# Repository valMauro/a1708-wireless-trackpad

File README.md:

# A1708 Wireless Trackpad

**Turn the Force Touch trackpad of a MacBook Pro (A1708, 13" 2016–2017) into a standalone
USB / Bluetooth trackpad, with Mac-style 1:1 gestures.**

*[Leggi in italiano](README.it.md)*

A Raspberry Pi Pico W talks to the trackpad over its native SPI protocol and presents it to the
computer as a **Windows Precision Touchpad** (PTP), over USB, classic Bluetooth or Bluetooth Low
Energy. Windows supports it natively. On macOS, which ignores third-party PTP devices, a small menu-bar app
([macos-trackpad-companion](https://github.com/mathias-sm/macos-trackpad-companion), patched for
this project) turns the raw touches into real macOS gestures: desktop swipes, Mission Control,
pinch, rotate and smooth scrolling that follow the fingers 1:1.

## Features

- **Original Apple hardware**: same glass, same Force Touch click with haptic feedback (generated
  by the trackpad itself).
- **Three connections**: USB-C cable, classic Bluetooth, or **Bluetooth Low Energy** with the
  standard Battery Service, so the battery level shows up in the macOS battery widget and in Windows
  settings.
- **Three paired computers** with one-press switching (like Logitech Easy-Switch), each with its
  own white LED.
- **18650 Li-ion battery** with USB-C charging, a power button, battery indication on the LEDs,
  power saving and an automatic rest mode.
- **Mac-like feel on macOS**: the companion patch uses the *exact* pointer and scroll
  acceleration curves of a MacBook's built-in trackpad, read from macOS itself.
- **Robust firmware**: message validation as in the Linux `applespi` driver, filtering of the
  touch glitches the trackpad produces while vibrating, de-bounced clicks.
- **Firmware updates through the USB-C port** with the case closed: hold buttons 1 and 3 while
  plugging in the cable.
- **All-in-one PCB** (KiCad, ready for JLCPCB assembly) and a **3D-printable wedge case**.

## How it works

```
 A1708 trackpad ──SPI (4 MHz) + 3.3 V / 5 V / 12 V──▶  all-in-one board
                                                         ├─ Raspberry Pi Pico W (firmware)
                                                         ├─ TP4056 charger + 18650 cell
                                                         ├─ MT3608 boost 5 V
                                                         └─ Pololu U3V16F12 boost 12 V (haptics)
        │
        ├─ USB HID ─────────────┐
        ├─ Bluetooth Classic ───┼──▶ Windows: native Precision Touchpad
        └─ Bluetooth LE (HOGP) ─┘    macOS:  Trackpad Companion app ──▶ native gestures
```

## Repository layout

| Folder | Contents |
|---|---|
| [`firmware/`](firmware) | Pico W firmware (C, pico-sdk, TinyUSB, BTstack) and prebuilt `.uf2` files |
| [`hardware/pcb/`](hardware/pcb) | KiCad board, Gerbers, BOM and placement files for JLCPCB |
| [`hardware/case/`](hardware/case) | STL files of the case and their Python source |
| [`macos-companion/`](macos-companion) | Patch for macos-trackpad-companion and a build script |
| [`docs/`](docs) | Build guide, firmware manual, macOS setup, SPI protocol notes |

## Getting started

1. **Read the [hardware guide](docs/en/hardware.md)**: parts list, PCB ordering and the two small
   hand modifications the current board needs.
2. **Flash the firmware**: copy `firmware/prebuilt/trackpad-a1708_pico_w.uf2` to the Pico W
   ([firmware manual](docs/en/firmware.md)).
3. **Print and assemble the case** ([assembly guide](docs/en/assembly.md)).
4. **Pair it**: hold button 1 for 3 seconds and look for "Trackpad A1708" in the Bluetooth settings.
5. **On a Mac**, build and install the companion app ([macOS guide](docs/en/macos.md)).

Documentation: [hardware](docs/en/hardware.md) · [assembly](docs/en/assembly.md) ·
[firmware](docs/en/firmware.md) · [macOS](docs/en/macos.md) · [SPI protocol](docs/en/protocol.md)

## Status and known limitations

This is a working personal build, shared as is. Things worth knowing:

- **Board revision v2 needs two hand modifications**: a wire that feeds the 12 V converter from the
  battery instead of the 5 V rail (without it, clicks are unreliable), and two wires for USB data.
  Both are described with pictures in the hardware guide.
- **Battery life** is roughly 20 hours of continuous use and about 30 hours left on idle with a
  3000 mAh cell (measured: ~86 mA in use, ~49 mA idle, ~38 mA in rest mode at 5 V). The Pico W
  and its radio set the floor; switch it off with the button when you are done.
- **Tested on**: macOS 27 (USB, classic Bluetooth, BLE) and Windows (USB and classic Bluetooth).
  BLE on Windows should work but has not been tested yet.
- **Pico W (RP2040)** is the tested board. A build for the Pico 2 W is provided, but the latest
  firmware has not been tested on it.
- On macOS, "shake mouse pointer to locate" does not trigger, because the pointer is moved by the
  companion app with synthetic events.
- The USB IDs are the pid.codes test pair `1209:0001`, fine for personal use. If you make and
  distribute devices, get your own.
- Code comments and some drawings are in Italian; the documentation is in English and Italian.

## Credits

- The SPI protocol and message format come from the Linux
  [`applespi`](https://github.com/torvalds/linux/blob/master/drivers/input/keyboard/applespi.c)
  driver, plus logic-analyser captures of a real MacBook.
- [macos-trackpad-companion](https://github.com/mathias-sm/macos-trackpad-companion) by its authors
  (MIT OR Apache-2.0): the macOS gesture engine this project builds on.
- The macOS 27 Dock-swipe event layout follows the work of
  [Mac Mouse Fix](https://github.com/noah-nuebling/mac-mouse-fix) and OpenLogi.
- Raspberry Pi [pico-sdk](https://github.com/raspberrypi/pico-sdk),
  [TinyUSB](https://github.com/hathach/tinyusb), [BTstack](https://github.com/bluekitchen/btstack).

## License

Firmware, hardware design files, case and documentation: **GNU GPL v3.0** (see [LICENSE](LICENSE)).

Exceptions:
- The companion patch in [`macos-companion/`](macos-companion) uses the upstream license,
  **MIT OR Apache-2.0**, so it can be merged back upstream.
- Third-party libraries keep their own licenses: pico-sdk (BSD-3-Clause), TinyUSB (MIT) and BTstack.
  BTstack is free for non-commercial use; on Raspberry Pi Pico W and Pico 2 W it is also covered by
  Raspberry Pi's licence agreement with BlueKitchen. Check its terms before any commercial use.

Author: **valMauro**

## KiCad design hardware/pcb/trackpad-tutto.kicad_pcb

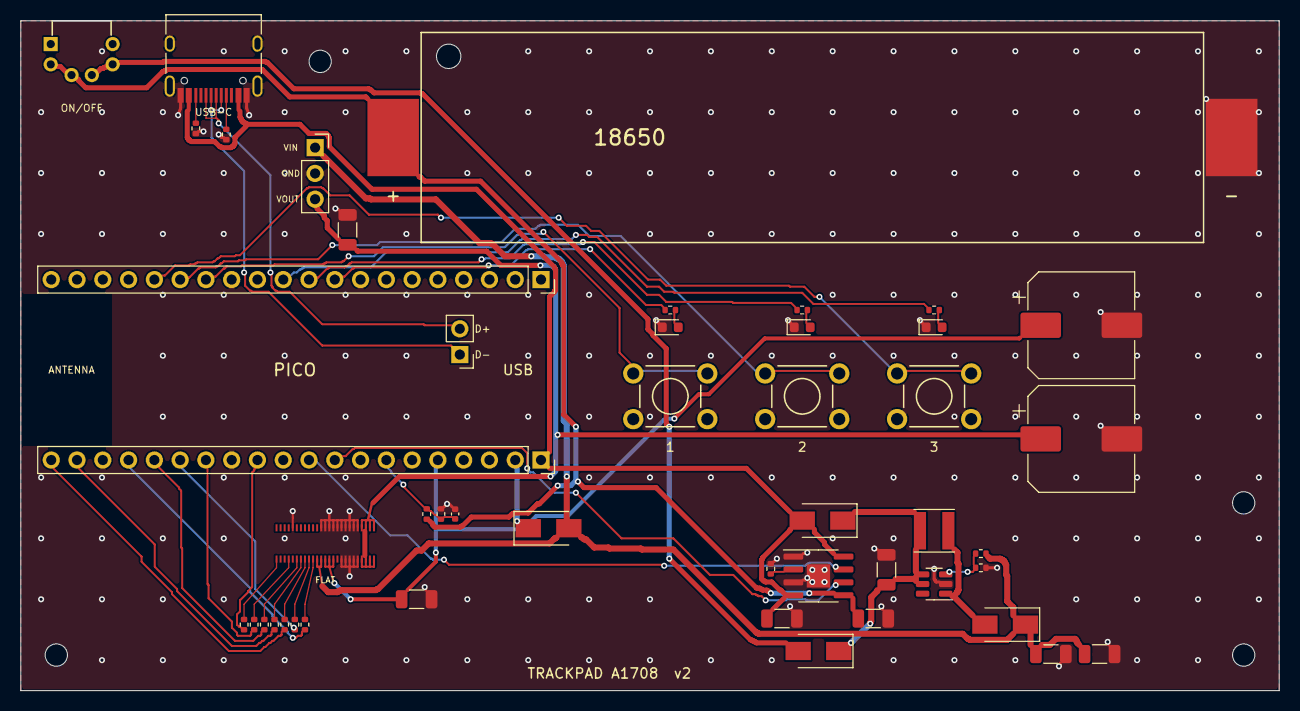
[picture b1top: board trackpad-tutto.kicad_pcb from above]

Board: 2 copper layers, 124.0 x 66.0 mm, 52 parts (0 on the bottom side), 42 nets.

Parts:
BT1: BH-18650-B1BA002
C1, C2, C3, C4, C5, C7, C9: 22uF 25V; C_1206_3216Metric
C6, C8: 470uF 25V; CP_Elec_10x10
C10: 100nF; C_0402_1005Metric
D1, D2, D3: SS14; D_SMA
D4: SS34; D_SMA
D5, D6, D7: LED; LED_0603_1608Metric
H1, H2, H3, H4: M2; MountingHole_2.2mm_M2
J1: DF40C-50DS-0.4V(51); DF40C-50DS-0.4V
J2, J3: Presa Pico 1x20; PinSocket_1x20_P2.54mm_Vertical
J6: POLOLU 12V; PinSocket_1x03_P2.54mm_Vertical
J7: USB D-/D+; PinHeader_1x02_P2.54mm_Vertical
J8: USB-C; USB_C_Receptacle_HRO_TYPE-C-31-M-12
L1: 22uH; L_Taiyo-Yuden_NR-40xx
R1: 2k; R_0402_1005Metric
R2: 7.5k; R_0402_1005Metric
R3: 1k; R_0402_1005Metric
R4, R5: 100k; R_0402_1005Metric
R6, R7, R8, R9, R10, R11, R12: 330; R_0402_1005Metric
R13, R14, R15: 100; R_0402_1005Metric
R16, R17: 5.1k; R_0402_1005Metric
SW1, SW2, SW3: TASTO 12mm; SW_TACT_6x6_LS7.3
SW4: PB-22E77-S-E
U1: TP4056; HSOP-8-1EP_3.9x4.9mm_P1.27mm_EP2.3x2.3mm
U2: MT3608; SOT-23-6

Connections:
ADC: C10.1, J3.7, R4.2, R5.1
BATP: BT1.2, C2.1, R4.1, SW4.2, SW4.3, U1.5
BTN1: J2.14, SW1.1, SW1.2
BTN2: J2.15, SW2.1, SW2.2
BTN3: J2.16, SW3.1, SW3.2
CC1: J8.A5, R17.1
CC2: J8.B5, R16.1
CHRG: J3.10, U1.7
CLK_P: J3.17, R12.2
CLK_T: J1.B10, R12.1
CS_P: J3.19, R9.2
CS_T: J1.B7, R9.1
DM: J7.1, J8.A7, J8.B7
DP: J7.2, J8.A6, J8.B6
FB: R2.1, R3.1, U2.3
GND: BT1.1, C1.2, C2.2, C3.2, C4.2, C5.2, C6.2, C7.2, C8.2, C9.2, C10.2, D5.1, D6.1, D7.1, J1.A5, J1.A12, J1.A13, J1.A14, J1.A15, J1.A16, J1.A17, J1.A18, J1.A19, J1.A20, J1.A21, J1.B17, J1.B18, J1.B19, J1.B20, J1.B21, J2.3, J2.8, J2.13, J2.18, J3.3, J3.8, J3.13, J3.18, J6.2, J8.A1, J8.A12, J8.B1, J8.B12, J8.S1, R1.2, R3.2, R5.2, R16.2, R17.2, SW1.3, SW1.4, SW2.3, SW2.4, SW3.3, SW3.4, U1.1, U1.3, U1.9, U2.2
IFEN_P: J3.15, R11.2
IFEN_T: J1.B9, R11.1
INT_P: J3.14, R7.2
INT_T: J1.B4, R7.1
LED1: J2.9, R13.1
LED2: J2.10, R14.1
LED3: J2.11, R15.1
LEDA1: D5.2, R13.2
LEDA2: D6.2, R14.2
LEDA3: D7.2, R15.2
LID_P: J3.12, R6.2
LID_T: J1.B1, R6.1
MISO_P: J3.20, R10.2
MISO_T: J1.B8, R10.1
MOSI_P: J3.16, R8.2
MOSI_T: J1.B6, R8.1
NODE: C3.1, D1.1, D2.1, L1.1, U2.4, U2.5
PROG: R1.1, U1.2
STDBY: J3.9, U1.6
SWN: D4.2, L1.2, U2.1
SWO: D2.2, SW4.5, SW4.6
V3V3: C8.1, C9.1, J1.B13, J1.B14, J1.B15, J3.5
V5: C4.1, C5.1, D3.2, D4.1, J1.B11, J1.B12, J6.1, R2.2
V12: C6.1, C7.1, J1.A22, J1.A23, J1.A24, J1.A25, J1.B22, J1.B23, J1.B24, J1.B25, J6.3
VBUS: C1.1, D1.2, J3.1, J8.A4, J8.A9, J8.B4, J8.B9, U1.4, U1.8
VSYS: D3.1, J3.2

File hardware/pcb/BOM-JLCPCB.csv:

Comment,Designator,Footprint,LCSC Part #
BH-18650-B5BA008,BT1,BATTERY-SMD_18650-1S-L77.1-W20.7,C5371777
100nF,C10,0402,C1525
22uF 25V,"C7,C9,C1,C2,C3,C4,C5",1206,C12891
470uF 25V,"C8,C6","SMD,D10xL10.2mm",C3351
SS14,"D3,D1,D2",SMA,C2480
SS34,D4,SMA,C8678
LED,"D5,D6,D7",0603,C2290
DF40C-50DS-0.4V(51),J1,DF40C-50DS-0.4V,C424646
Presa Pico 1x20,"J2,J3",PinSocket_1x20_P2.54mm,C25503124
POLOLU 12V,J6,PinSocket_1x03_P2.54mm,C146243
USB-C,J8,USB-C SMD 16P,C165948
22uH,L1,4x4mm,C83472
2k,R1,0402,C4109
100,"R13,R14,R15",0402,C25076
5.1k,"R16,R17",0402,C25905
7.5k,R2,0402,C25918
1k,R3,0402,C11702
100k,"R4,R5",0402,C25741
330,"R6,R7,R8,R9,R10,R11,R12",0402,C25104
TASTO 12mm,"SW1,SW2,SW3",KEY-TH_4P-L6.4-W6.0-P4.50-LS7.3,C2681506
PB-22E77-S-E,SW4,SW-TH_PB-22E77,C7428711
TP4056,U1,ESOP-8,C16581
MT3608,U2,SOT-23-6,C84817
